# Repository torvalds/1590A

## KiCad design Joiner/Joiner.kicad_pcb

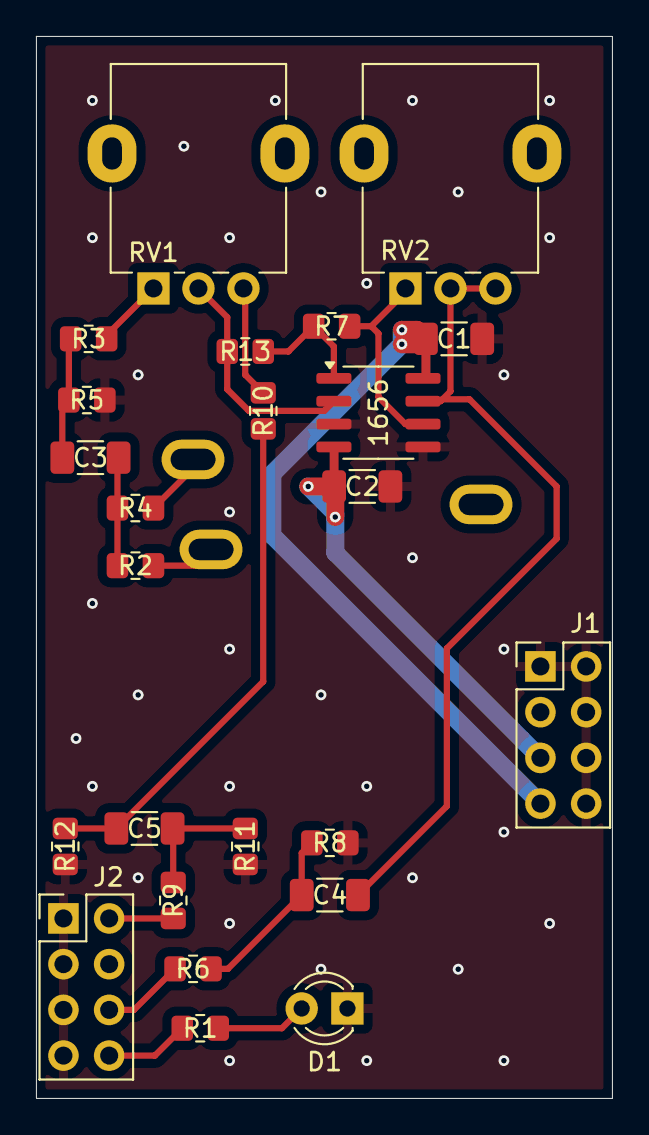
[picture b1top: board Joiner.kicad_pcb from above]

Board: 4 copper layers, 32.0 x 59.0 mm, 26 parts (1 on the bottom side), 20 nets.

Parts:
Box1: 1590A
C1, C2, C3, C5: 0.1uF; C_1206_3216Metric_Pad1.33x1.80mm_HandSolder
C4: 1uF; C_1206_3216Metric_Pad1.33x1.80mm_HandSolder
D1: LED; LED_D3.0mm
J1, J2: Conn_02x04_Odd_Even; PinHeader_2x04_P2.54mm_Vertical
J3: AudioJack2_Ground; CK-6.35
R1, R2, R3, R6, R7, R9, R10, R13: 10k; R_0805_2012Metric_Pad1.20x1.40mm_HandSolder
R4, R11: 1M0; R_0805_2012Metric_Pad1.20x1.40mm_HandSolder
R5, R8, R12: 470k; R_0805_2012Metric_Pad1.20x1.40mm_HandSolder
RV1: B10k; Potentiometer_Alpha_RD901F-40-00D_Single_Vertical
RV2: A25k; Potentiometer_Alpha_RD901F-40-00D_Single_Vertical
U1: OPA1656; SOIC-8_3.9x4.9mm_P1.27mm

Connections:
+V: C1.1, J1.7, U1.8 (V+)
-V: C2.1, J1.5, U1.4 (V-)
GND: C1.2, C2.2, D1.1 (K), J1.1, J1.2, J1.4, J1.6, J1.8, J2.1, J2.3, J2.5, J2.7, R5.2, R8.2, R11.2, R12.2, U1.3 (+), U1.5 (+)
GND2: J3.G, J3.S, R4.2
IN^{2}: J3.T, R2.1
IN^{RAW}: J2.2, R9.1
LED: J2.8, R1.1
unnamed: C3.1, R2.2, R4.1
unnamed: C3.2, R3.1, R5.1
unnamed: C4.2, R6.1, R8.1
unnamed: C5.1, R9.2, R11.1
unnamed: C5.2, R10.1, R12.1
unnamed: D1.2 (A), R1.2
unnamed: R3.2, RV1.1
unnamed: R10.2, RV1.3
unnamed: R13.1, RV1.2, U1.2 (-)
unnamed: R7.1, R13.2, U1.1 (OUT)
unnamed: R7.2, RV2.1, U1.6 (-)
unnamed: C4.1, RV2.2, RV2.3, U1.7 (OUT)
OUT^{EFF}: J2.6, R6.2

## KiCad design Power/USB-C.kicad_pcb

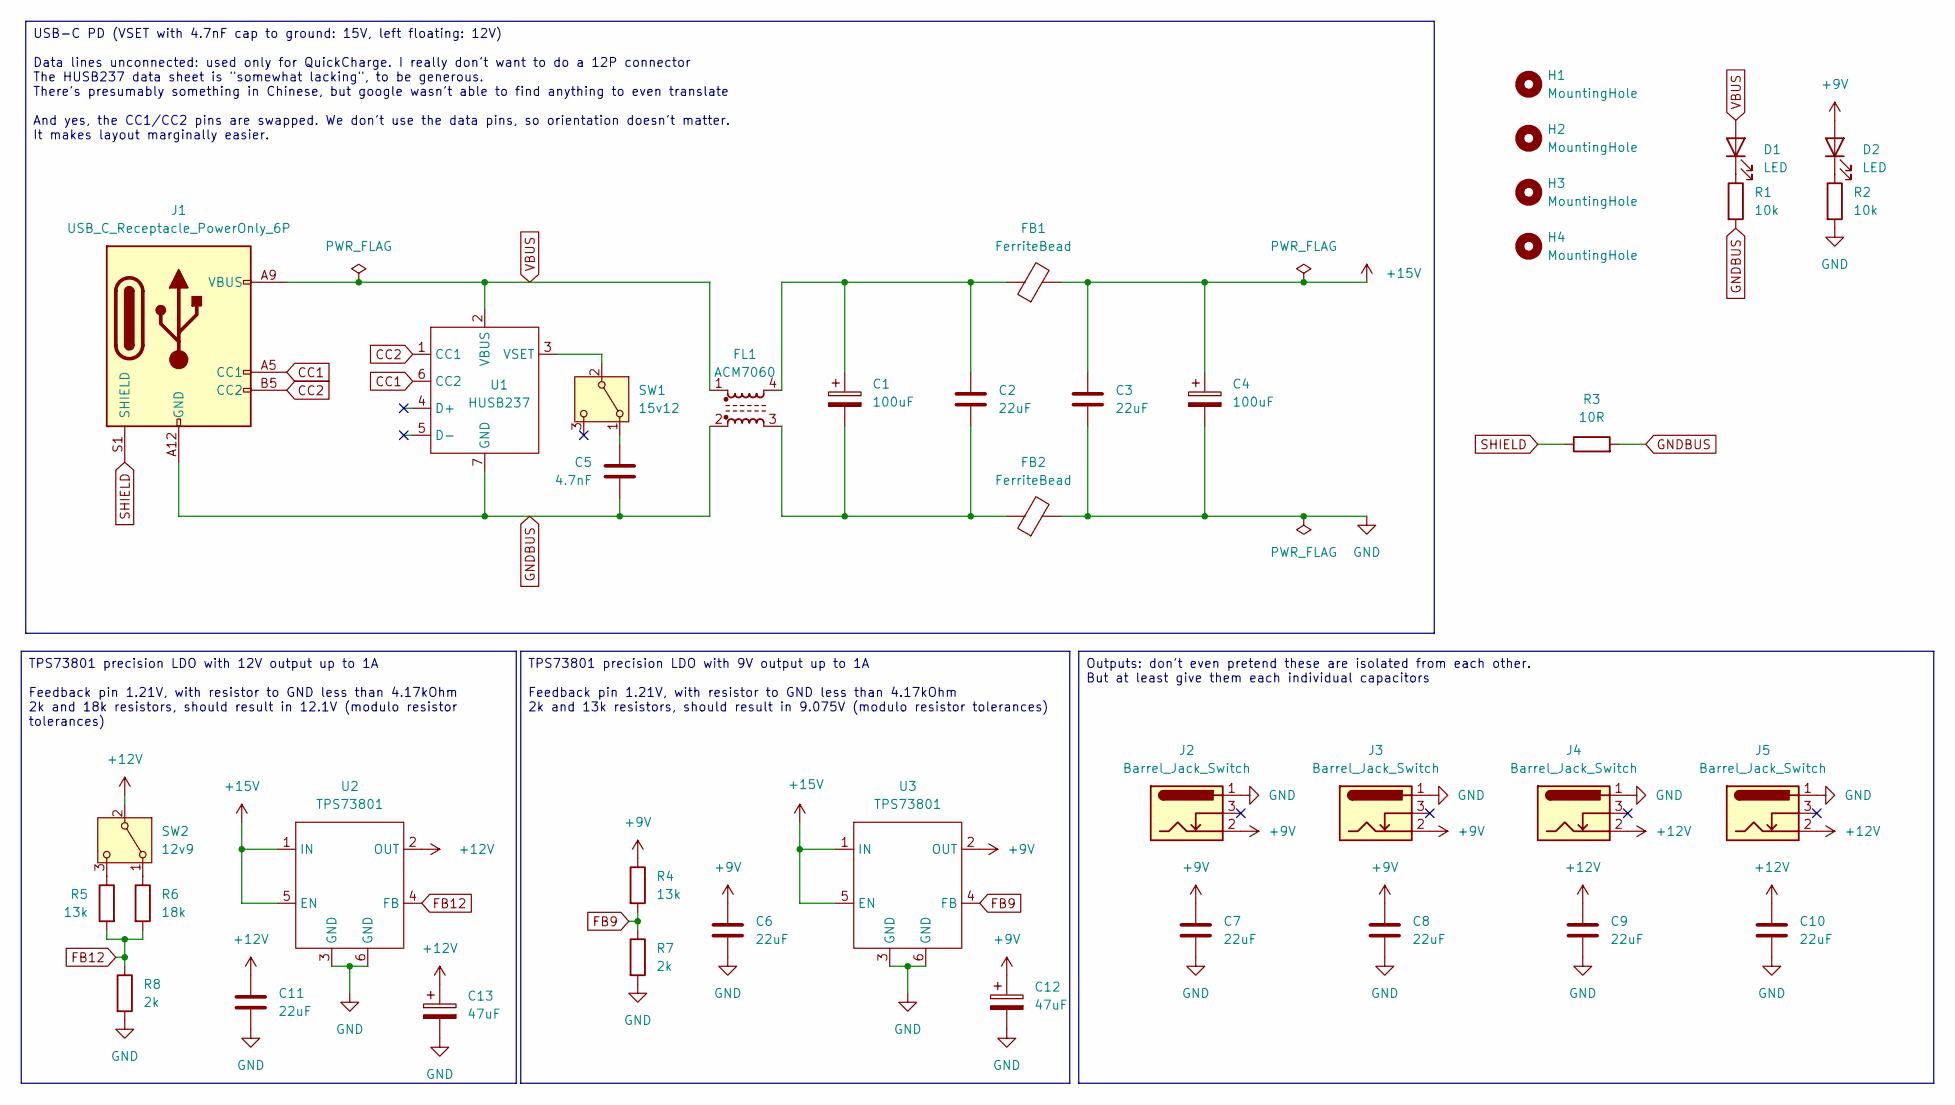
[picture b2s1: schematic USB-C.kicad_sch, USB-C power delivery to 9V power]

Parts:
C1, C4: 100uF; CP_Radial_D8.0mm_P3.50mm
C2, C3, C6, C7, C8, C9, C10, C11: 22uF; C_1206_3216Metric_Pad1.33x1.80mm_HandSolder
C5: 4.7nF; C_0805_2012Metric_Pad1.18x1.45mm_HandSolder
C12, C13: 47uF; CP_Radial_D5.0mm_P2.00mm
D1, D2: LED; Würth Reverse Mount LED
FB1, FB2: FerriteBead; L_1206_3216Metric_Pad1.22x1.90mm_HandSolder
FL1: ACM7060; L_CommonModeChoke_TDK_ACM7060
H1, H2, H3, H4: MountingHole; MountingHole_3mm
J1: USB_C_Receptacle_PowerOnly_6P; USB_C_Receptacle_GCT_USB4125-xx-x-0190_6P_TopMnt_Horizontal
J2, J3, J4, J5: Barrel_Jack_Switch; BarrelJack_Wuerth_6941xx301002
R1, R2: 10k; R_0805_2012Metric_Pad1.20x1.40mm_HandSolder
R3: 10R; R_0805_2012Metric_Pad1.20x1.40mm_HandSolder
R4, R5: 13k; R_0805_2012Metric_Pad1.20x1.40mm_HandSolder
R6: 18k; R_0805_2012Metric_Pad1.20x1.40mm_HandSolder
R7, R8: 2k; R_0805_2012Metric_Pad1.20x1.40mm_HandSolder
SW1: 15v12; PinSocket_1x03_P2.54mm_Vertical
SW2: 12v9; PinSocket_1x03_P2.54mm_Vertical
U1: HUSB237; WSON-6-1EP_2x2mm_P0.65mm_EP1x1.6mm
U2, U3: TPS73801; SOT-223-6

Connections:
+9V: C6.1, C7.1, C8.1, C12.1, D2.2 (A), J2.2, J3.2, R4.1, U3.2 (OUT)
+12V: C9.1, C10.1, C11.1, C13.1, J4.2, J5.2, SW2.2 (B), U2.2 (OUT)
+15V: C3.1, C4.1, FB1.2, U2.1 (IN), U2.5 (EN), U3.1 (IN), U3.5 (EN)
CC1: J1.A5 (CC1), U1.6 (CC2)
CC2: J1.B5 (CC2), U1.1 (CC1)
FB9: R4.2, R7.1, U3.4 (FB)
FB12: R5.2, R6.2, R8.1, U2.4 (FB)
GND: C3.2, C4.2, C6.2, C7.2, C8.2, C9.2, C10.2, C11.2, C12.2, C13.2, FB2.2, J2.1, J3.1, J4.1, J5.1, R2.2, R7.2, R8.2, U2.3 (GND), U2.6 (GND), U3.3 (GND), U3.6 (GND)
GNDBUS: C5.2, FL1.2, J1.A12 (GND), J1.B12 (GND), R1.2, R3.2, U1.7 (GND)
unnamed: C1.1, C2.1, FB1.1, FL1.4
unnamed: C1.2, C2.2, FB2.1, FL1.3
unnamed: D1.1 (K), R1.1
unnamed: D2.1 (K), R2.1
unnamed: C5.1, SW1.1 (A)
unnamed: SW1.2 (B), U1.3 (VSET)
unnamed: R6.1, SW2.1 (A)
unnamed: R5.1, SW2.3 (C)
SHIELD: J1.S1 (SHIELD), R3.1
VBUS: D1.2 (A), FL1.1, J1.A9 (VBUS), J1.B9 (VBUS), U1.2 (VBUS)

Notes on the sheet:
TPS73801 precision LDO with 9V output up to 1A Feedback pin 1.21V, with resistor to GND less than 4.17kOhm 2k and 13k resistors, should result in 9.075V (modulo resistor tolerances)
TPS73801 precision LDO with 12V output up to 1A Feedback pin 1.21V, with resistor to GND less than 4.17kOhm 2k and 18k resistors, should result in 12.1V (modulo resistor tolerances)
Outputs: don't even pretend these are isolated from each other. But at least give them each individual capacitors
USB-C PD (VSET with 4.7nF cap to ground: 15V, left floating: 12V) Data lines unconnected: used only for QuickCharge. I really don't want to do a 12P connector The HUSB237 data sheet is "somewhat lacking", to be generous. There's presumably something in Chinese, but google wasn't able to find anythi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

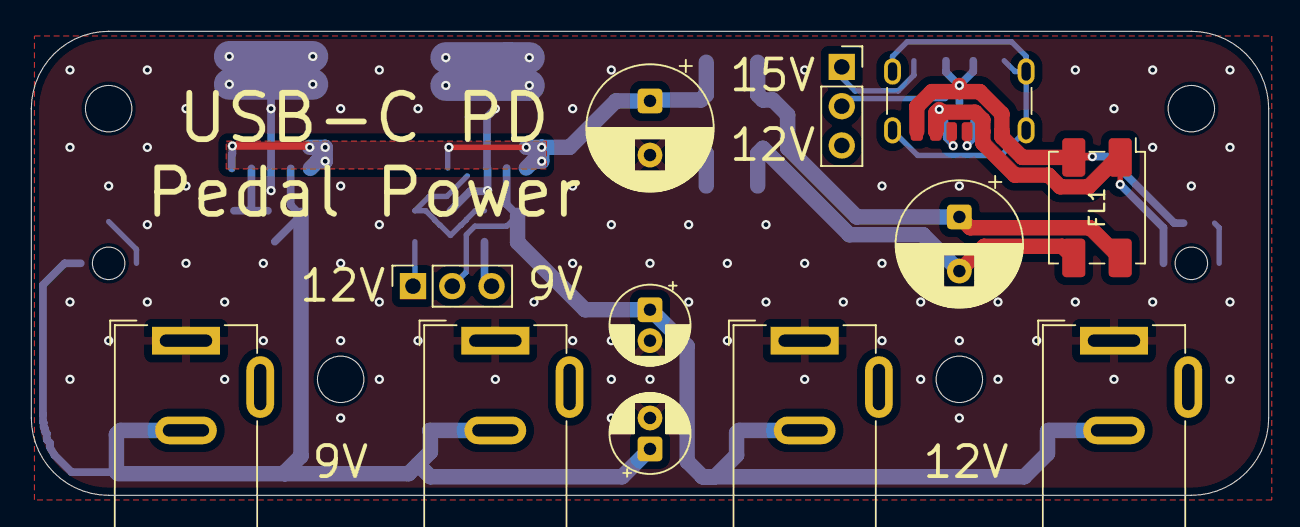
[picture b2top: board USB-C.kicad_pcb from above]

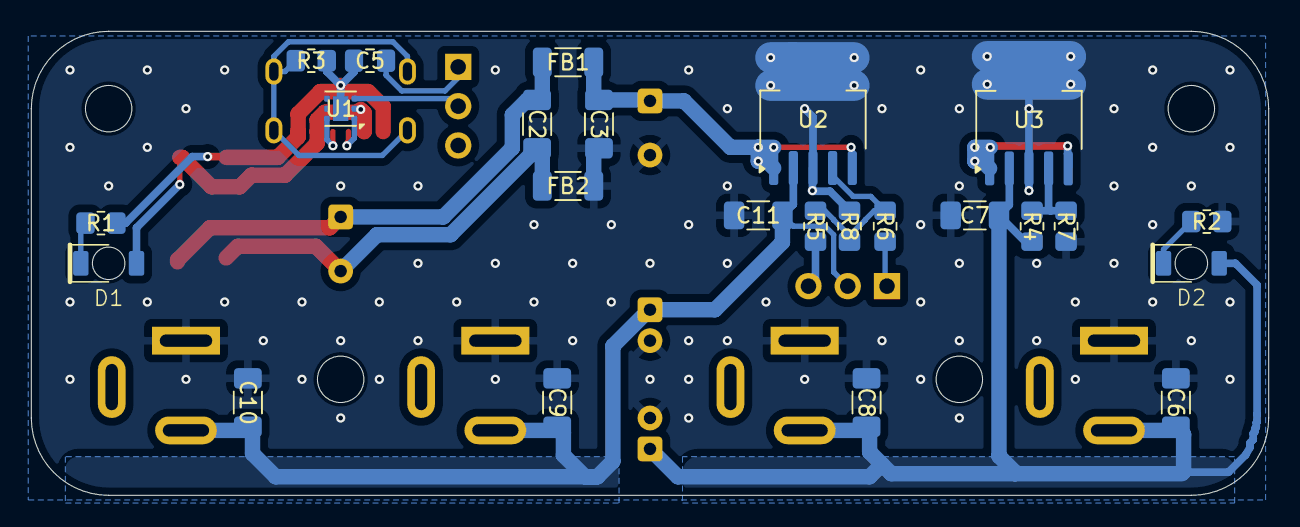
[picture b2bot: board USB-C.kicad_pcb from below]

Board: 2 copper layers, 80.0 x 30.0 mm, 40 parts (24 on the bottom side), 19 nets.

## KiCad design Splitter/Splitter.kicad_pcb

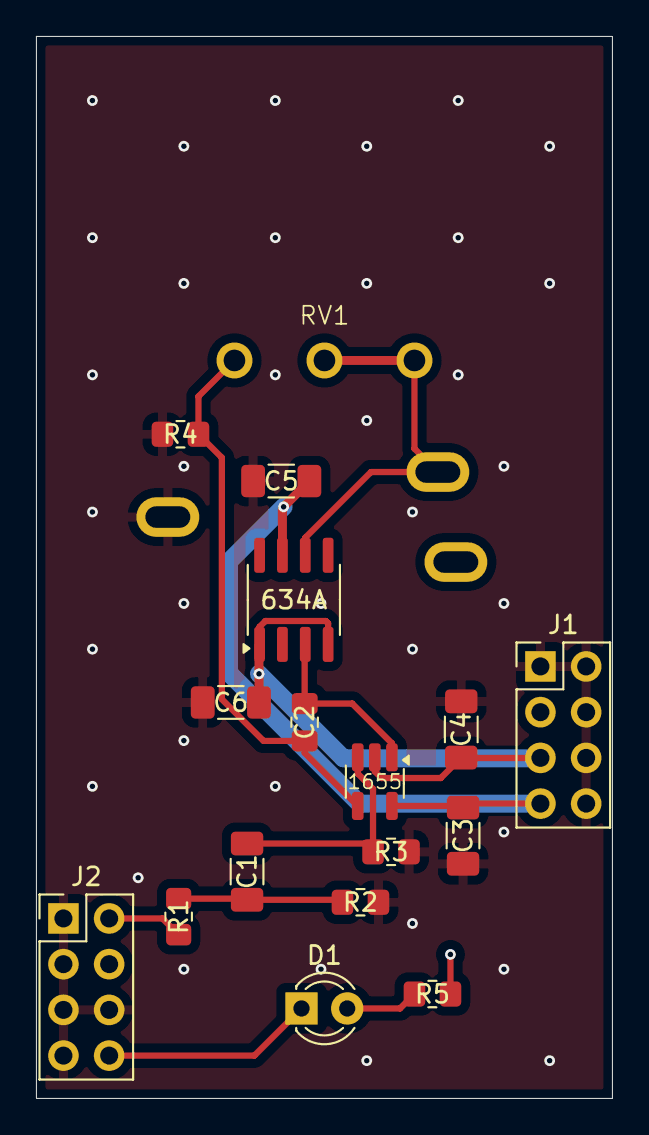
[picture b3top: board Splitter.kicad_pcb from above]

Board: 4 copper layers, 32.0 x 59.0 mm, 19 parts (1 on the bottom side), 12 nets.

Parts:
Box1: 1590A
C1: 1uF; C_1206_3216Metric_Pad1.33x1.80mm_HandSolder
C2: 10pF; C_0805_2012Metric_Pad1.18x1.45mm_HandSolder
C3, C4: 0.1uF; C_1206_3216Metric_Pad1.33x1.80mm_HandSolder
C5, C6: 10uF; C_1206_3216Metric_Pad1.33x1.80mm_HandSolder
D1: LED; LED_D3.0mm
J1, J2: Conn_02x04_Odd_Even; PinHeader_2x04_P2.54mm_Vertical
J3: AudioJack2_Ground; CK-6.35
R1, R4, R5: 10k; R_0805_2012Metric_Pad1.20x1.40mm_HandSolder
R2: 1M0; R_0805_2012Metric_Pad1.20x1.40mm_HandSolder
R3: 470k; R_0805_2012Metric_Pad1.20x1.40mm_HandSolder
RV1: 10kA; Potentiometer-Basic
U1: OPA1655; SOT-23-5_HandSoldering
U2: BUF634AxD; SOIC-8_3.9x4.9mm_P1.27mm

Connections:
+V: C3.1, C5.1, J1.7, U1.5 (V+), U2.7 (V+)
-V: C4.1, C6.1, J1.5, U1.2 (V-), U2.1 (BW), U2.4 (V-)
GND: C3.2, C4.2, C5.2, C6.2, J1.1, J1.2, J1.4, J1.6, J1.8, J2.1, J2.3, J2.5, J2.6, J2.7, J3.G, R2.2, R3.2, R4.1
IN^{RAW}: J2.2, R1.1
LED: D1.1 (K), J2.8
unnamed: C1.1, R1.2, R2.1
unnamed: D1.2 (A), R5.2
unnamed: J3.T, RV1.2, RV1.3, U2.6
unnamed: C1.2, R3.1, U1.3 (+)
unnamed: C2.2, R4.2, RV1.1, U1.4 (-)
unnamed: C2.1, U1.1, U2.3 (V_{IN})
VIN: J1.3, R5.1

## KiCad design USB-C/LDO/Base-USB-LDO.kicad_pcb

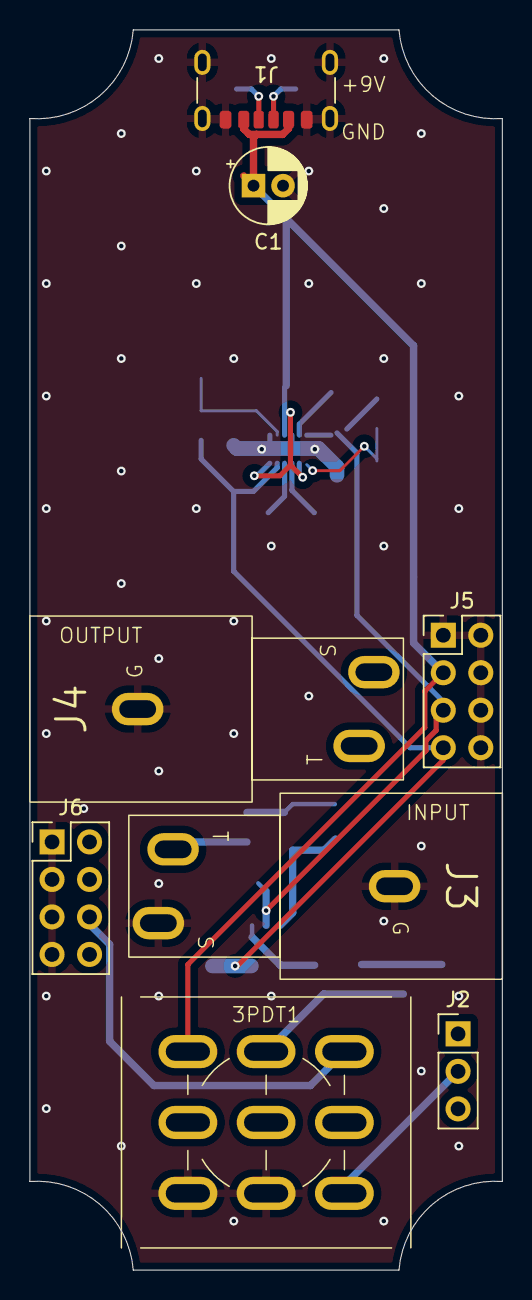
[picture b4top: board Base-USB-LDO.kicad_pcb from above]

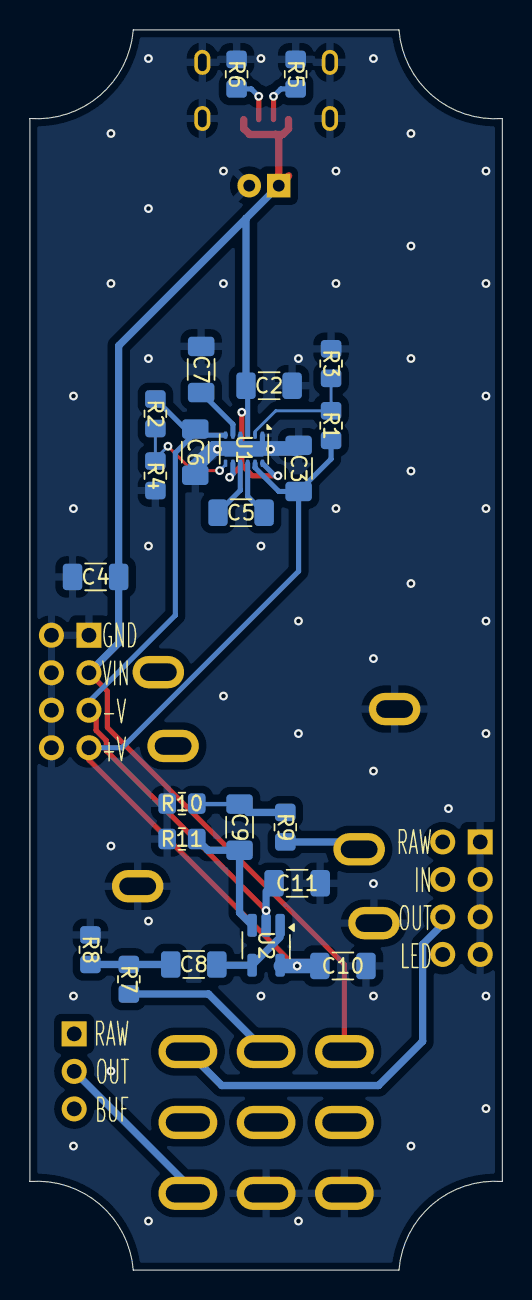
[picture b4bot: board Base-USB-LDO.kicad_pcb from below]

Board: 4 copper layers, 32.0 x 84.0 mm, 32 parts (23 on the bottom side), 22 nets.

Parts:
3PDT1: 3PDT-Stomp-Switch
Box1: 1590A
C1: 47uF; CP_Radial_D5.0mm_P2.00mm
C2, C7: 4.7uF; C_1206_3216Metric_Pad1.33x1.80mm_HandSolder
C3, C6: 2.2uF; C_1206_3216Metric_Pad1.33x1.80mm_HandSolder
C4, C5, C8: 1uF; C_1206_3216Metric_Pad1.33x1.80mm_HandSolder
C9, C10, C11: 0.1uF; C_1206_3216Metric_Pad1.33x1.80mm_HandSolder
J1: USB_C_Receptacle_PowerOnly_6P; USB_C_Receptacle_GCT_USB4125-xx-x-0190_6P_TopMnt_Horizontal
J2: Conn_01x03_Pin; PinHeader_1x03_P2.54mm_Vertical
J3, J4: AudioJack2_Ground; CK-6.35
J5, J6: Conn_02x04_Odd_Even; PinHeader_2x04_P2.54mm_Vertical
R1, R2: 200k; R_0805_2012Metric_Pad1.20x1.40mm_HandSolder
R3, R4: 82k; R_0805_2012Metric_Pad1.20x1.40mm_HandSolder
R5, R6: 5k1; R_0805_2012Metric_Pad1.20x1.40mm_HandSolder
R7, R9: 10k; R_0805_2012Metric_Pad1.20x1.40mm_HandSolder
R8, R11: 470k; R_0805_2012Metric_Pad1.20x1.40mm_HandSolder
R10: 1M0; R_0805_2012Metric_Pad1.20x1.40mm_HandSolder
U1: LM27762; WSON-12-1EP_3x2mm_P0.5mm_EP1x2.65
U2: OPA1655; SOT-23-5_HandSoldering

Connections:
+V: C3.1, C10.1, J5.7, R1.1, U1.11 (OUT+), U2.5 (V+)
-V: C6.1, C11.1, J5.5, R2.1, U1.6 (OUT-), U2.2 (V-)
BUFFERED: 3PDT1.4 (B1), J2.3, R7.2
FB+: R1.2, R3.1, U1.2 (FB+)
FB-: R2.2, R4.1, U1.7 (FB-)
GND: 3PDT1.3 (A3), 3PDT1.6 (B3), C1.2, C2.2, C3.2, C4.2, C6.2, C7.2, C10.2, C11.2, J1.A12 (GND), J1.B12 (GND), J1.S1 (SHIELD), J3.G, J3.S, J4.G, J5.1, J5.2, J5.4, J5.6, J5.8, J6.1, J6.3, J6.5, J6.7, R3.2, R4.2, R5.2, R6.2, R8.2, R10.2, R11.2, U1.1 (PGOOD), U1.4 (GND), U1.13 (PAD)
IN: C9.2, R11.1, U2.3 (+)
IN^{EFF}: 3PDT1.5 (B2), J6.4
IN^{RAW}: J2.1, J3.T, J6.2, R9.1
LED: 3PDT1.2 (A2), J6.8
unnamed: C8.2, R7.1, R8.1
unnamed: C9.1, R9.2, R10.1
unnamed: J1.A5 (CC1), R6.1
unnamed: J1.B5 (CC2), R5.1
unnamed: C5.2, U1.10 (C+)
unnamed: C5.1, U1.9 (C-)
unnamed: C7.1, U1.5 (CP)
unnamed: C8.1, U2.1, U2.4 (-)
OUT^{EFF}: 3PDT1.7 (C1), J6.6
OUT^{RAW_OR_BUF}: 3PDT1.9 (C3), J2.2
OUT^{RAW}: 3PDT1.8 (C2), J4.T
VIN: 3PDT1.1 (A1), C1.1, C2.1, C4.1, J1.A9 (VBUS), J1.B9 (VBUS), J5.3, U1.3 (VIN), U1.8 (EN-), U1.12 (EN+)

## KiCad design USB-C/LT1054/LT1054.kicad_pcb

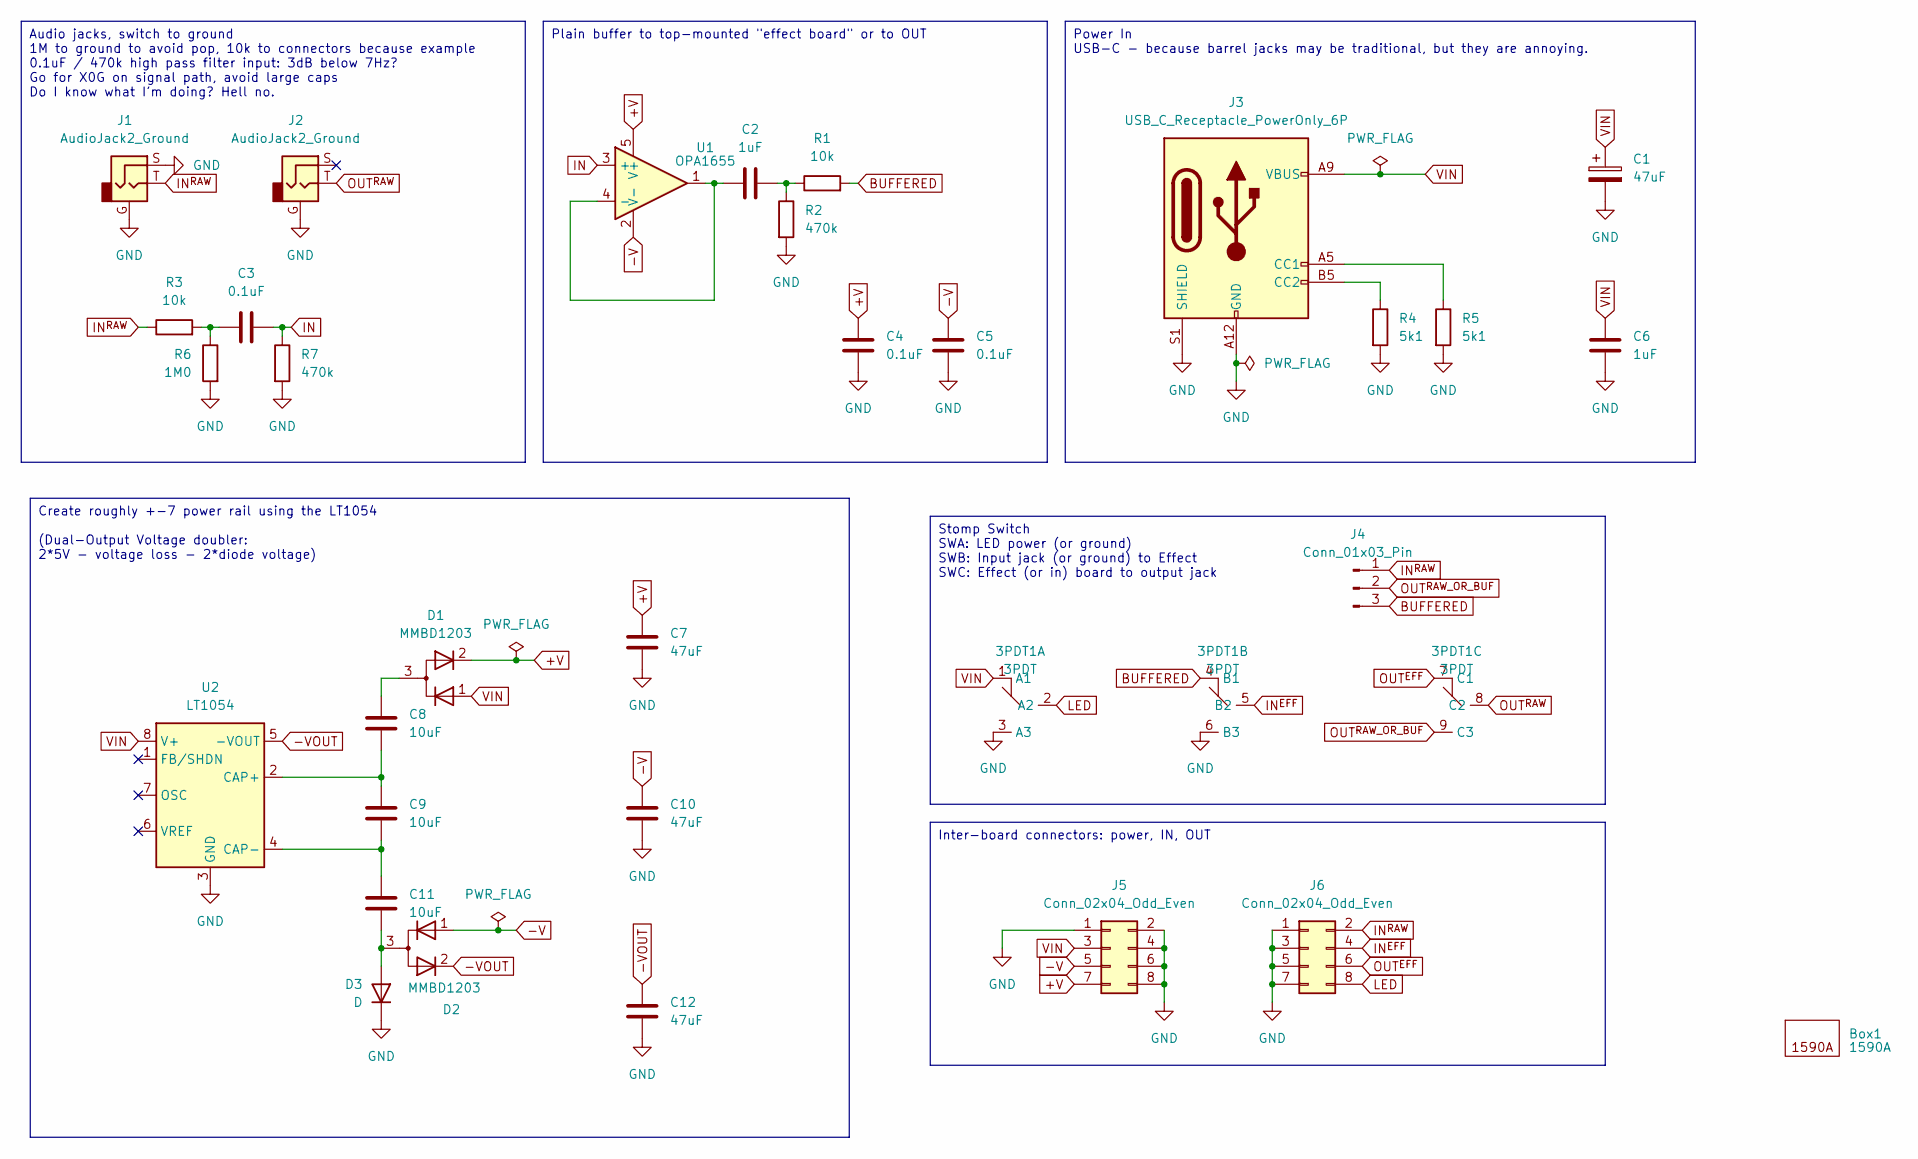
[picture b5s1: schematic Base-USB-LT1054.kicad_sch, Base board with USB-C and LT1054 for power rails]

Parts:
3PDT1: 3PDT; 3PDT-Stomp-Switch
Box1: 1590A
C1: 47uF; CP_Radial_D5.0mm_P2.00mm
C2, C6: 1uF; C_1206_3216Metric_Pad1.33x1.80mm_HandSolder
C3, C4, C5: 0.1uF; C_1206_3216Metric_Pad1.33x1.80mm_HandSolder
C7, C10, C12: 47uF; C_1206_3216Metric_Pad1.33x1.80mm_HandSolder
C8, C9, C11: 10uF; C_1206_3216Metric_Pad1.33x1.80mm_HandSolder
D1, D2: MMBD1203; SOT-23-3
D3: D; D_SOD-123
J1, J2: AudioJack2_Ground; CK-6.35
J3: USB_C_Receptacle_PowerOnly_6P; USB_C_Receptacle_GCT_USB4125-xx-x-0190_6P_TopMnt_Horizontal
J4: Conn_01x03_Pin; PinHeader_1x03_P2.54mm_Vertical
J5, J6: Conn_02x04_Odd_Even; PinHeader_2x04_P2.54mm_Vertical
R1, R3: 10k; R_0805_2012Metric_Pad1.20x1.40mm_HandSolder
R2, R7: 470k; R_0805_2012Metric_Pad1.20x1.40mm_HandSolder
R4, R5: 5k1; R_0805_2012Metric_Pad1.20x1.40mm_HandSolder
R6: 1M0; R_0805_2012Metric_Pad1.20x1.40mm_HandSolder
U1: OPA1655; SOT-23-5_HandSoldering
U2: LT1054; SOIC-8_3.9x4.9mm_P1.27mm

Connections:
+V: C4.1, C7.1, D1.2 (K), J5.7, U1.5 (V+)
-V: C5.1, C10.1, D2.1 (A), J5.5, U1.2 (V-)
-VOUT: C12.1, D2.2 (K), U2.5 (-VOUT)
BUFFERED: 3PDT1.4 (B1), J4.3, R1.2
GND: 3PDT1.3 (A3), 3PDT1.6 (B3), C1.2, C4.2, C5.2, C6.2, C7.2, C10.2, C12.2, D3.1 (K), J1.G, J1.S, J2.G, J3.A12 (GND), J3.B12 (GND), J3.S1 (SHIELD), J5.1, J5.2, J5.4, J5.6, J5.8, J6.1, J6.3, J6.5, J6.7, R2.2, R4.2, R5.2, R6.2, R7.2, U2.3 (GND)
IN: C3.2, R7.1, U1.3 (+)
IN^{EFF}: 3PDT1.5 (B2), J6.4
IN^{RAW}: J1.T, J4.1, J6.2, R3.1
LED: 3PDT1.2 (A2), J6.8
unnamed: C2.2, R1.1, R2.1
unnamed: C3.1, R3.2, R6.1
unnamed: C8.1, D1.3 (common)
unnamed: C11.2, D2.3 (common), D3.2 (A)
unnamed: J3.A5 (CC1), R5.1
unnamed: J3.B5 (CC2), R4.1
unnamed: C2.1, U1.1, U1.4 (-)
unnamed: C8.2, C9.1, U2.2 (CAP+)
unnamed: C9.2, C11.1, U2.4 (CAP-)
OUT^{EFF}: 3PDT1.7 (C1), J6.6
OUT^{RAW_OR_BUF}: 3PDT1.9 (C3), J4.2
OUT^{RAW}: 3PDT1.8 (C2), J2.T
VIN: 3PDT1.1 (A1), C1.1, C6.1, D1.1 (A), J3.A9 (VBUS), J3.B9 (VBUS), J5.3, U2.8 (V+)

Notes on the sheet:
Audio jacks, switch to ground 1M to ground to avoid pop, 10k to connectors because example 0.1uF / 470k high pass filter input: 3dB below 7Hz? Go for X0G on signal path, avoid large caps Do I know what I'm doing? Hell no.
Power In USB-C - because barrel jacks may be traditional, but they are annoying.
Plain buffer to top-mounted "effect board" or to OUT
Inter-board connectors: power, IN, OUT
Stomp Switch SWA: LED power (or ground) SWB: Input jack (or ground) to Effect SWC: Effect (or in) board to output jack
Create roughly +-7 power rail using the LT1054 (Dual-Output Voltage doubler: 2*5V - voltage loss - 2*diode voltage)

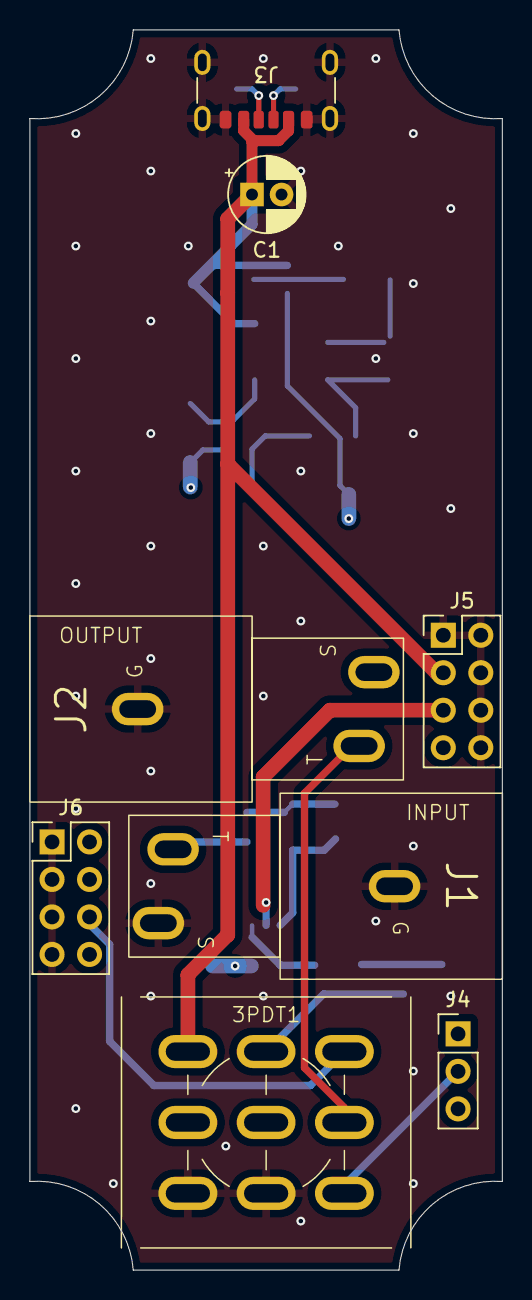
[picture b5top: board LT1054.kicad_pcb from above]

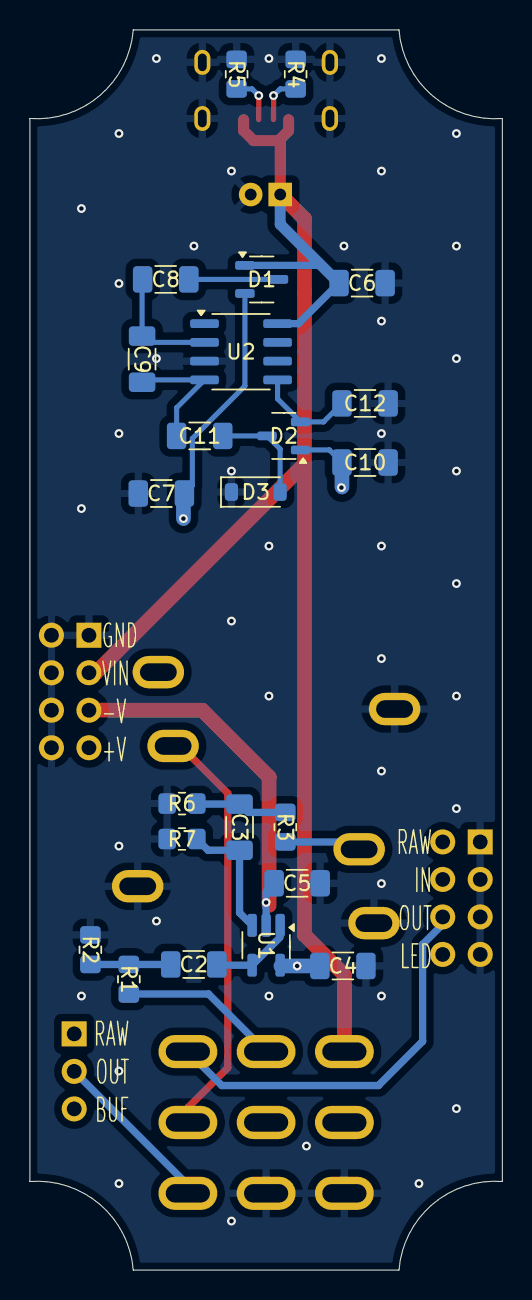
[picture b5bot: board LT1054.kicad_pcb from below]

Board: 4 copper layers, 32.0 x 84.0 mm, 32 parts (23 on the bottom side), 22 nets.

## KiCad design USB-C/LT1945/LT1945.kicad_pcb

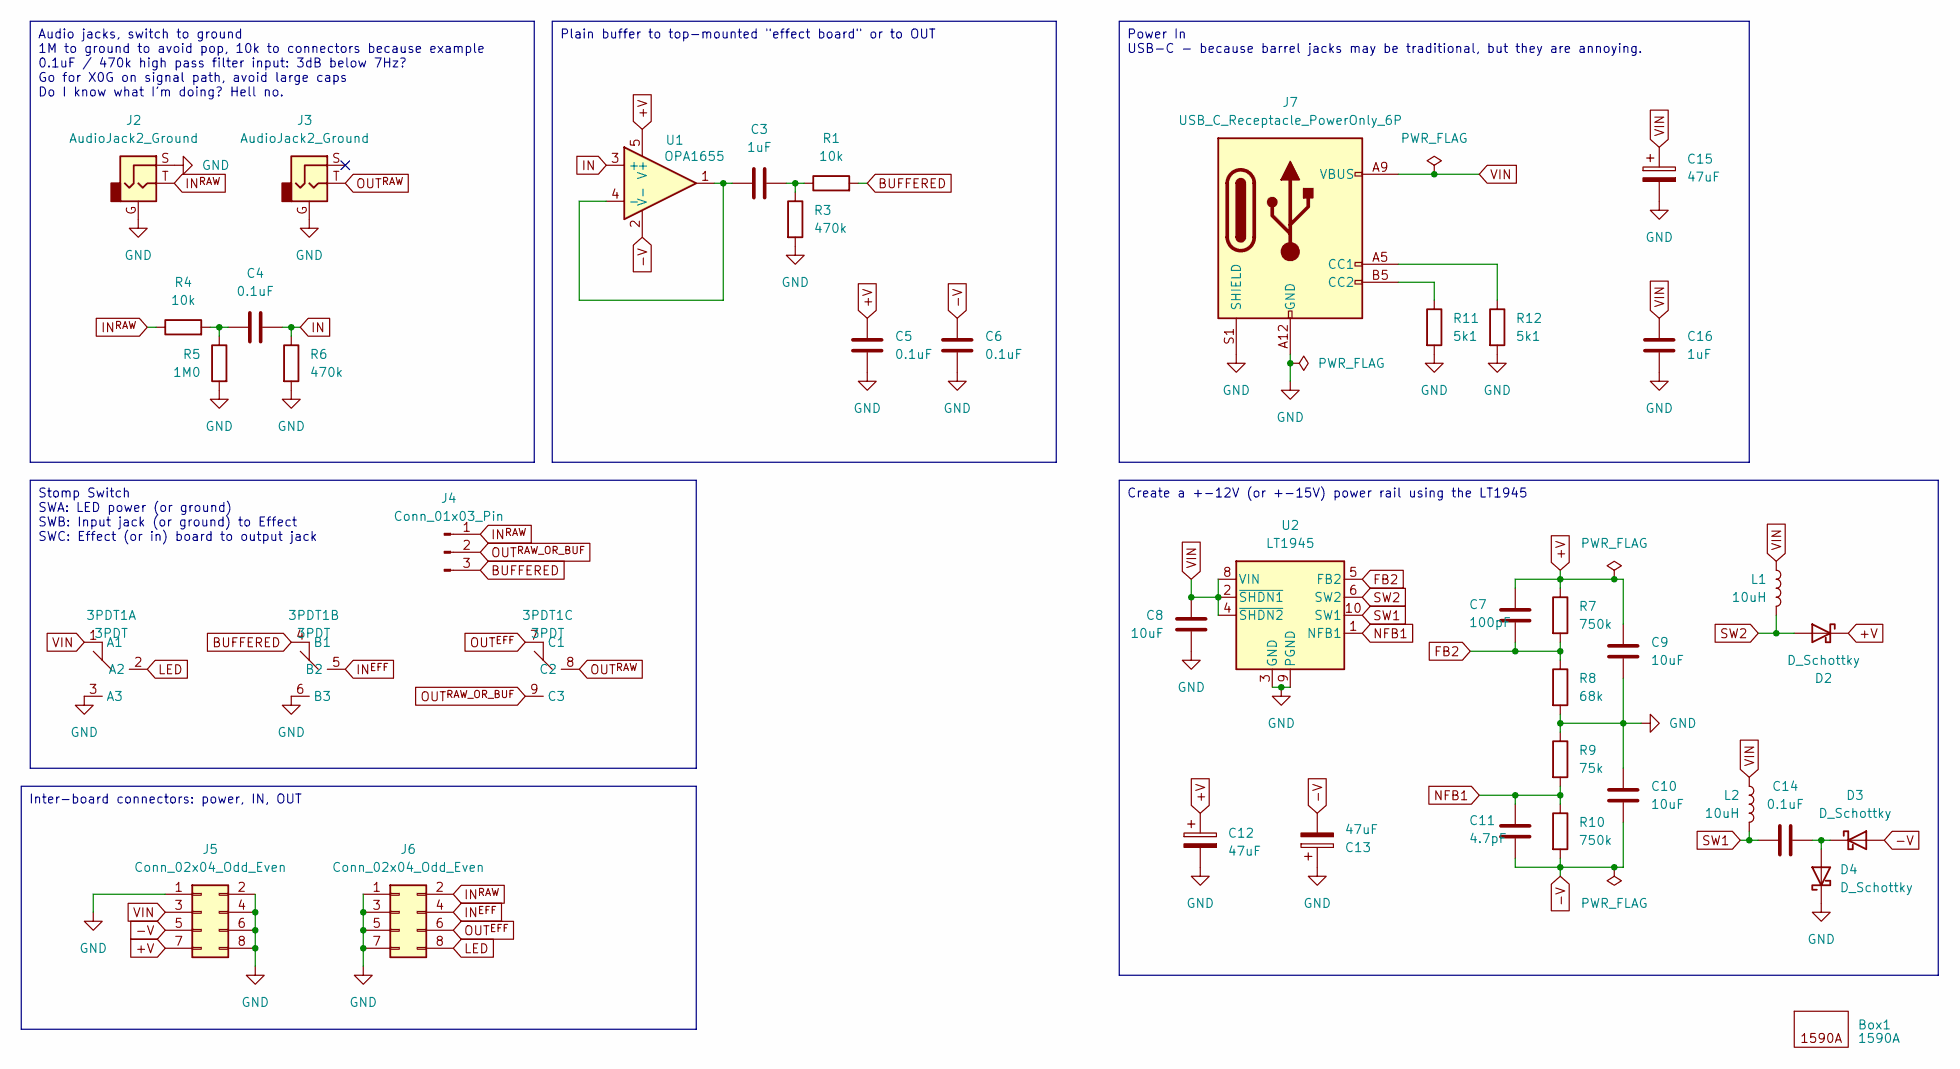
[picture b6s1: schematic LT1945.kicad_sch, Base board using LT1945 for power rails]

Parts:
3PDT1: 3PDT; 3PDT-Stomp-Switch
Box1: 1590A
C3, C16: 1uF; C_1206_3216Metric_Pad1.33x1.80mm_HandSolder
C4, C5, C6, C14: 0.1uF; C_1206_3216Metric_Pad1.33x1.80mm_HandSolder
C7: 100pF; C_0805_2012Metric_Pad1.18x1.45mm_HandSolder
C8, C9, C10: 10uF; C_1206_3216Metric_Pad1.33x1.80mm_HandSolder
C11: 4.7pF; C_0805_2012Metric_Pad1.18x1.45mm_HandSolder
C12, C13: 47uF; CP_Radial_D4.0mm_P2.00mm
C15: 47uF; CP_Radial_D5.0mm_P2.00mm
D2, D3, D4: D_Schottky; D_SOD-123
J2, J3: AudioJack2_Ground; CK-6.35
J4: Conn_01x03_Pin; PinHeader_1x03_P2.54mm_Vertical
J5, J6: Conn_02x04_Odd_Even; PinHeader_2x04_P2.54mm_Vertical
J7: USB_C_Receptacle_PowerOnly_6P; USB_C_Receptacle_GCT_USB4125-xx-x-0190_6P_TopMnt_Horizontal
L1, L2: 10uH; L_0805_2012Metric_Pad1.15x1.40mm_HandSolder
R1, R4: 10k; R_0805_2012Metric_Pad1.20x1.40mm_HandSolder
R3, R6: 470k; R_0805_2012Metric_Pad1.20x1.40mm_HandSolder
R5: 1M0; R_0805_2012Metric_Pad1.20x1.40mm_HandSolder
R7, R10: 750k; R_0805_2012Metric_Pad1.20x1.40mm_HandSolder
R8: 68k; R_0805_2012Metric_Pad1.20x1.40mm_HandSolder
R9: 75k; R_0805_2012Metric_Pad1.20x1.40mm_HandSolder
R11, R12: 5k1; R_0805_2012Metric_Pad1.20x1.40mm_HandSolder
U1: OPA1655; SOT-23-5_HandSoldering
U2: LT1945; MSOP-10_3x3mm_P0.5mm

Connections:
+V: C5.1, C7.2, C9.1, C12.1, D2.1 (K), J5.7, R7.1, U1.5 (V+)
-V: C6.1, C10.2, C11.1, C13.2, D3.2 (A), J5.5, R10.2, U1.2 (V-)
BUFFERED: 3PDT1.4 (B1), J4.3, R1.2
FB2: C7.1, R7.2, R8.1, U2.5 (FB2)
GND: 3PDT1.3 (A3), 3PDT1.6 (B3), C5.2, C6.2, C8.2, C9.2, C10.1, C12.2, C13.1, C15.2, C16.2, D4.1 (K), J2.G, J2.S, J3.G, J5.1, J5.2, J5.4, J5.6, J5.8, J6.1, J6.3, J6.5, J6.7, J7.A12 (GND), J7.B12 (GND), J7.S1 (SHIELD), R3.2, R5.2, R6.2, R8.2, R9.1, R11.2, R12.2, U2.3 (GND), U2.7 (PGND), U2.9 (PGND)
IN: C4.2, R6.1, U1.3 (+)
IN^{EFF}: 3PDT1.5 (B2), J6.4
IN^{RAW}: J2.T, J4.1, J6.2, R4.1
LED: 3PDT1.2 (A2), J6.8
NFB1: C11.2, R9.2, R10.1, U2.1 (NFB1)
unnamed: C3.2, R1.1, R3.1
unnamed: C4.1, R4.2, R5.1
unnamed: C14.1, D3.1 (K), D4.2 (A)
unnamed: J7.A5 (CC1), R12.1
unnamed: J7.B5 (CC2), R11.1
unnamed: C3.1, U1.1, U1.4 (-)
OUT^{EFF}: 3PDT1.7 (C1), J6.6
OUT^{RAW_OR_BUF}: 3PDT1.9 (C3), J4.2
OUT^{RAW}: 3PDT1.8 (C2), J3.T
SW1: C14.2, L2.1, U2.10 (SW1)
SW2: D2.2 (A), L1.1, U2.6 (SW2)
VIN: 3PDT1.1 (A1), C8.1, C15.1, C16.1, J5.3, J7.A9 (VBUS), J7.B9 (VBUS), L1.2, L2.2, U2.2 (~SHDN1), U2.4 (~SHDN2), U2.8 (VIN)

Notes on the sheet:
Audio jacks, switch to ground 1M to ground to avoid pop, 10k to connectors because example 0.1uF / 470k high pass filter input: 3dB below 7Hz? Go for X0G on signal path, avoid large caps Do I know what I'm doing? Hell no.
Plain buffer to top-mounted "effect board" or to OUT
Inter-board connectors: power, IN, OUT
Stomp Switch SWA: LED power (or ground) SWB: Input jack (or ground) to Effect SWC: Effect (or in) board to output jack
Create a +-12V (or +-15V) power rail using the LT1945
Power In USB-C - because barrel jacks may be traditional, but they are annoying.

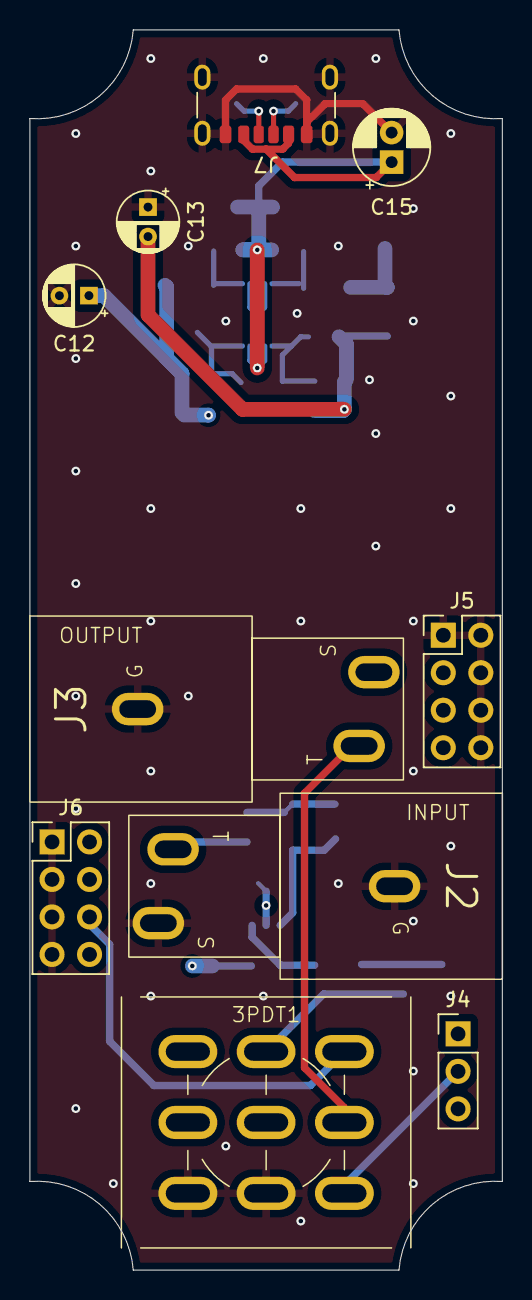
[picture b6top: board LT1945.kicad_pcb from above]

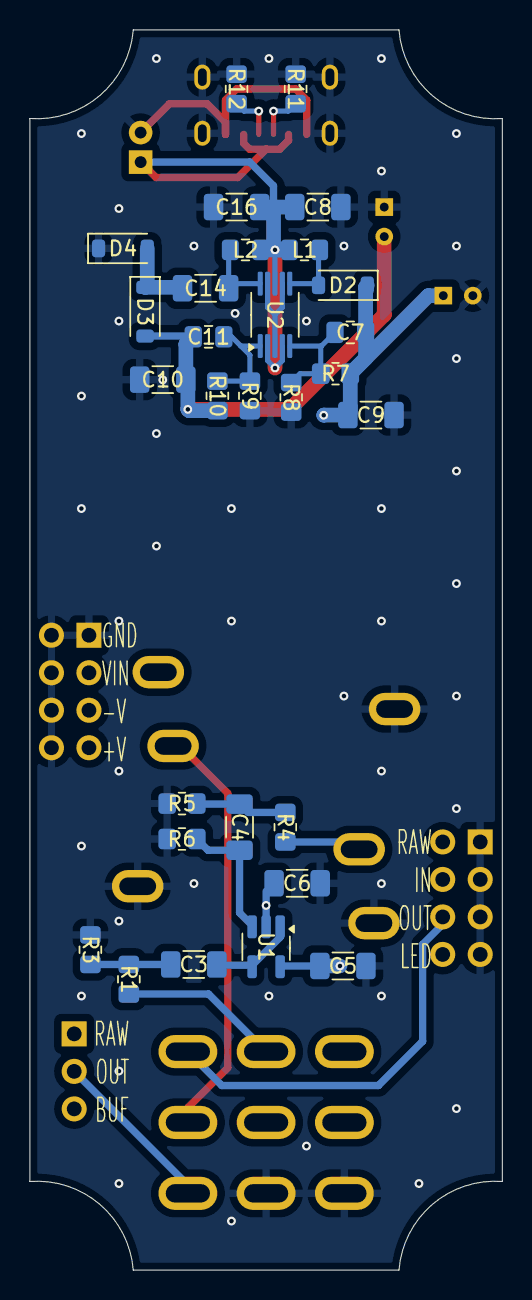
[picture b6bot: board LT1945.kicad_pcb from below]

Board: 4 copper layers, 32.0 x 84.0 mm, 40 parts (29 on the bottom side), 22 nets.
